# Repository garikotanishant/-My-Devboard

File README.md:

My devboard is a RP2040-based development board designed for prototyping and electronics projects. It features USB-C connectivity, onboard flash memory, a crystal oscillator for precise timing, and multiple GPIO pins for connecting sensors, LEDs, and other components. The board is laid out to support high-speed signals like USB-C while keeping power and ground distribution efficient, making it suitable for a simple microcontroller project! It was very complex for me to build (even with the instructions 😅) but it was a great first project and I learned a lot.

### PCB

### Schematic

##### 3D View

##### PCB parts checkout

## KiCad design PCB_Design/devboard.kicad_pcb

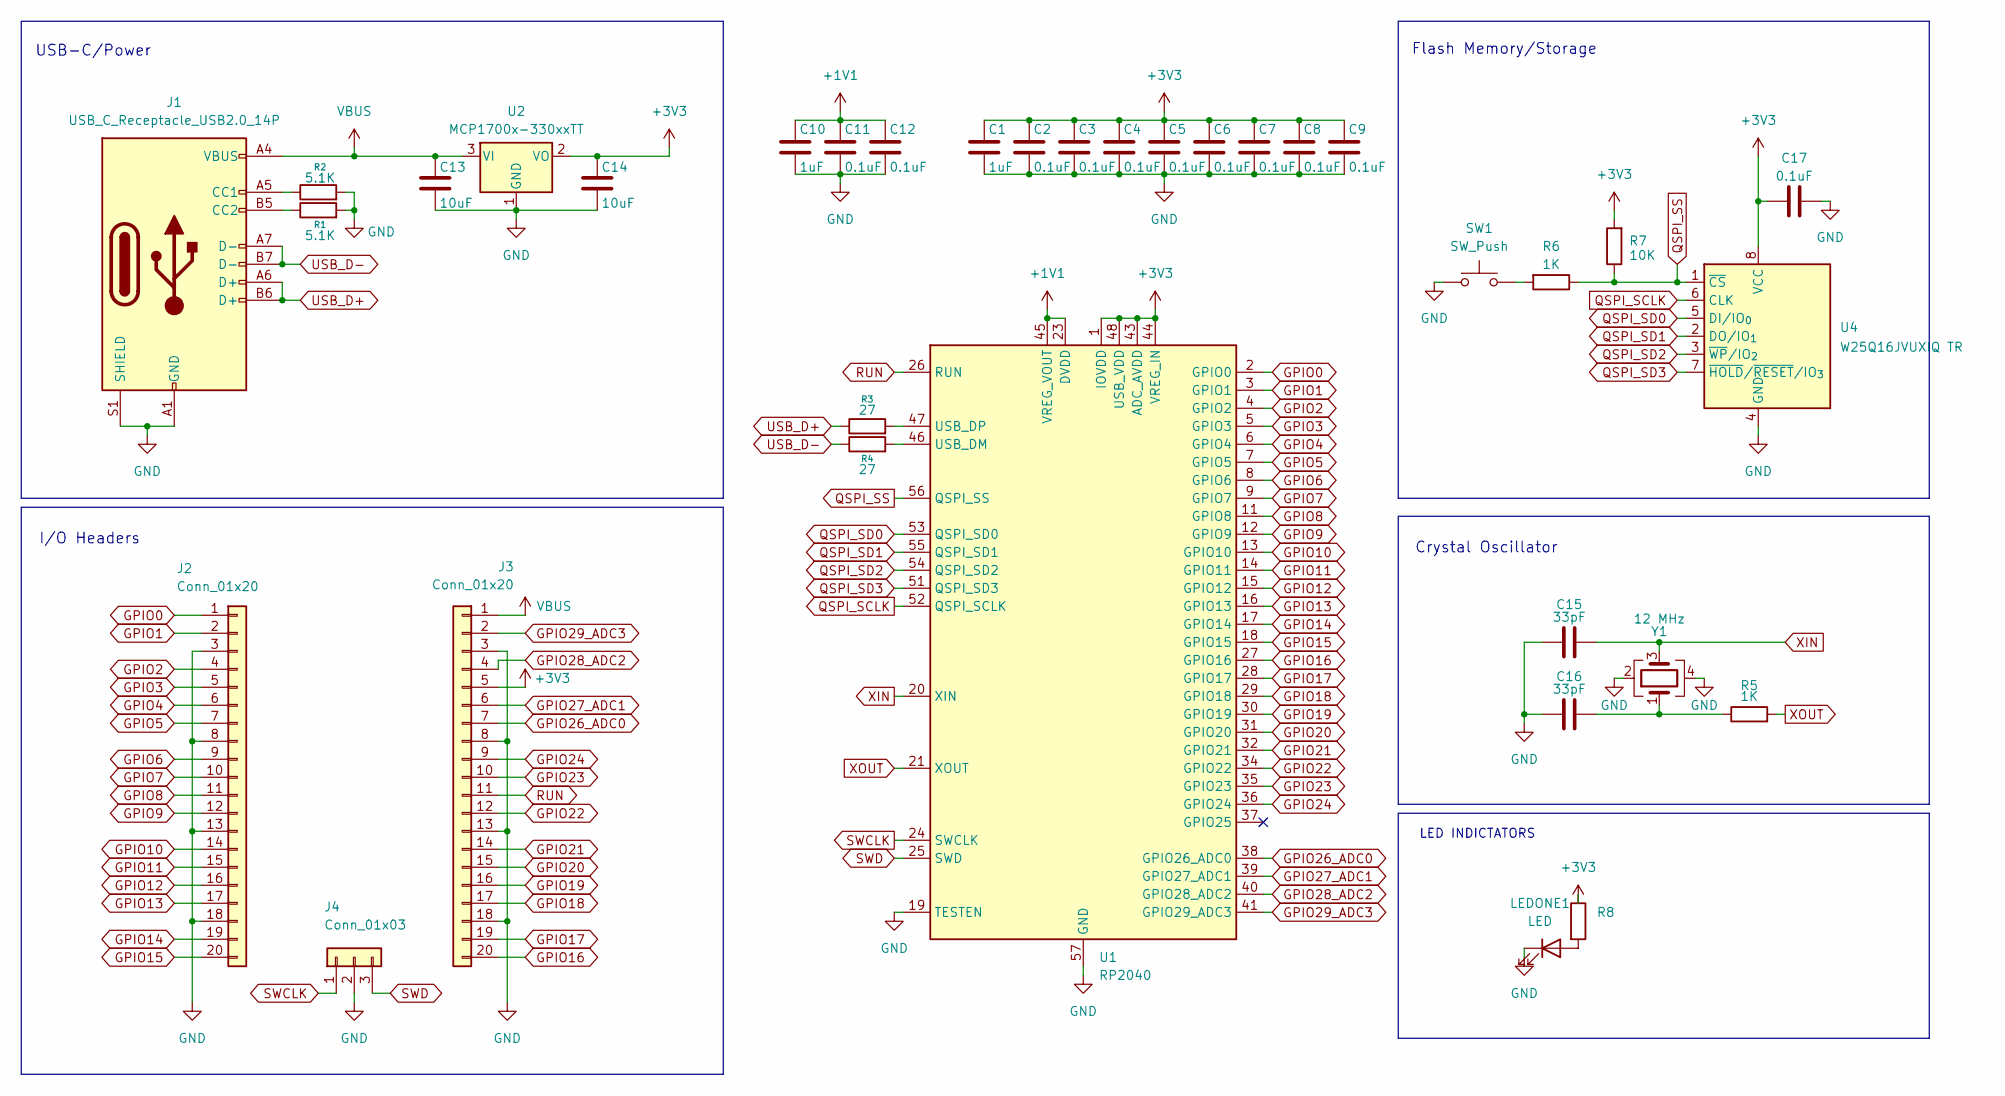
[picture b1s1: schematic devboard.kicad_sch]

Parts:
C1, C10: 1uF; C_0402_1005Metric
C2, C3, C4, C5, C6, C7, C8, C9, C11, C12, C17: 0.1uF; C_0402_1005Metric
C13, C14: 10uF; C_0603_1608Metric
C15, C16: 33pF; C_0402_1005Metric
J1: USB_C_Receptacle_USB2.0_14P; USB_C_Receptacle_HRO_TYPE-C-31-M-12
J2, J3: Conn_01x20; PinHeader_1x20_P2.54mm_Vertical
J4: Conn_01x03; PinHeader_1x03_P2.54mm_Vertical
LEDONE1: LED; LED_0603_1608Metric
R1, R2: 5.1K; R_0402_1005Metric
R3, R4: 27; R_0402_1005Metric
R5, R6: 1K; R_0402_1005Metric
R7: 10K; R_0402_1005Metric
R8: R; R_0603_1608Metric
SW1: SW_Push; SW_Push_SPST_NO_Alps_SKRK
U1: RP2040; QFN-56-1EP_7x7mm_P0.4mm_EP3.2x3.2mm
U2: MCP1700x-330xxTT; SOT-23
U4: W25Q16JVUXIQ TR; Winbond_USON-8-1EP_3x2mm_P0.5mm_EP0.2x1.6mm
Y1: 12 MHz; Crystal_SMD_3225-4Pin_3.2x2.5mm

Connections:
+1V1: C10.1, C11.1, C12.1, U1.23 (DVDD), U1.45 (VREG_VOUT), U1.50 (DVDD)
GND: C1.2, C2.2, C3.2, C4.2, C5.2, C6.2, C7.2, C8.2, C9.2, C10.2, C11.2, C12.2, C13.2, C14.2, C15.1, C16.1, C17.2, J1.A1 (GND), J1.A12 (GND), J1.B1 (GND), J1.B12 (GND), J1.S1 (SHIELD), J2.3, J2.8, J2.13, J2.18, J3.3, J3.8, J3.13, J3.18, J4.2, LEDONE1.1 (K), R1.2, R2.2, SW1.1, U1.19 (TESTEN), U1.57 (GND), U2.1 (GND), U4.4 (GND), Y1.2, Y1.4; also elsewhere on the board
GPIO1: J2.2, U1.3 (GPIO1)
GPIO2: J2.4, U1.4 (GPIO2)
GPIO3: J2.5, U1.5 (GPIO3)
GPIO4: J2.6, U1.6 (GPIO4)
GPIO5: J2.7, U1.7 (GPIO5)
GPIO6: J2.9, U1.8 (GPIO6)
GPIO7: J2.10, U1.9 (GPIO7)
GPIO8: J2.11, U1.11 (GPIO8)
GPIO9: J2.12, U1.12 (GPIO9)
GPIO10: J2.14, U1.13 (GPIO10)
GPIO11: J2.15, U1.14 (GPIO11)
GPIO12: J2.16, U1.15 (GPIO12)
GPIO13: J2.17, U1.16 (GPIO13)
GPIO14: J2.19, U1.17 (GPIO14)
GPIO15: J2.20, U1.18 (GPIO15)
GPIO16: J3.20, U1.27 (GPIO16)
GPIO17: J3.19, U1.28 (GPIO17)
GPIO18: J3.17, U1.29 (GPIO18)
GPIO19: J3.16, U1.30 (GPIO19)
GPIO20: J3.15, U1.31 (GPIO20)
GPIO21: J3.14, U1.32 (GPIO21)
GPIO22: J3.12, U1.34 (GPIO22)
GPIO23: J3.10, U1.35 (GPIO23)
GPIO24: J3.9, U1.36 (GPIO24)
GPIO26_ADC0: J3.7, U1.38 (GPIO26_ADC0)
GPIO27_ADC1: J3.6, U1.39 (GPIO27_ADC1)
GPIO28_ADC2: J3.4, U1.40 (GPIO28_ADC2)
GPIO29_ADC3: J3.2, U1.41 (GPIO29_ADC3)
unnamed: C16.2, R5.1, Y1.1
unnamed: J1.A5 (CC1), R2.1
unnamed: J1.B5 (CC2), R1.1
unnamed: LEDONE1.2 (A), R8.2
unnamed 34: R6.2, SW1.2; also elsewhere on the board
unnamed: R4.2, U1.46 (USB_DM)
unnamed: R3.2, U1.47 (USB_DP)
QSPI_SCLK: U1.52 (QSPI_SCLK), U4.6 (CLK)
QSPI_SD0: U1.53 (QSPI_SD0), U4.5 (DI/IO_{0})
QSPI_SD1: U1.55 (QSPI_SD1), U4.2 (DO/IO_{1})
QSPI_SD2: U1.54 (QSPI_SD2), U4.3 (~WP/IO_{2})
QSPI_SD3: U1.51 (QSPI_SD3), U4.7 (~HOLD/~RESET/IO_{3})
QSPI_SS: R6.1, R7.1, U1.56 (QSPI_SS), U4.1 (~CS)
RUN: J3.11, U1.26 (RUN)
SWCLK: J4.1, U1.24 (SWCLK)
SWD: J4.3, U1.25 (SWD)
USB_D+: J1.A6 (D+), J1.B6 (D+), R3.1
USB_D-: J1.A7 (D-), J1.B7 (D-), R4.1
VBUS: C13.1, J1.A4 (VBUS), J1.A9 (VBUS), J1.B4 (VBUS), J1.B9 (VBUS), J3.1, U2.3 (VI)
XIN: C15.2, U1.20 (XIN), Y1.3
XOUT: R5.2, U1.21 (XOUT)

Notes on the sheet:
Flash Memory/Storage
I/O Headers
LED INDICTATORS
Crystal Oscillator
USB-C/Power

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
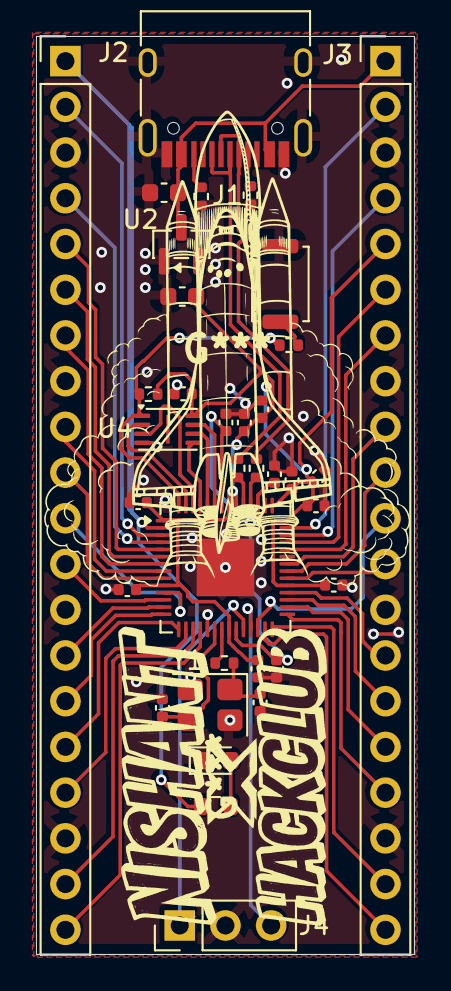
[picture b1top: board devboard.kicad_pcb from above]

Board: 2 copper layers, 21.0 x 51.0 mm, 35 parts (0 on the bottom side), 53 nets.

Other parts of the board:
Boot: SW_Push; SW_Push_SPST_NO_Alps_SKRK

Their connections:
GND: Boot.1; also elsewhere on the board
unnamed 34: Boot.2; also elsewhere on the board

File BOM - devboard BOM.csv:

Id,Designator,Footprint,Quantity,Comment,Supplier and ref
1,"C6,C5,C4,C2,C7,C11,C9,C12,C8,C17,C3",C_0402_1005Metric,11,0.1uF,
2,"C13,C14",C_0603_1608Metric,2,10uF,
16,Y1,Crystal_SMD_3225-4Pin_3.2x2.5mm,1,12 MHz,
4,"C1,C10",C_0402_1005Metric,2,1uF,
5,R7,R_0402_1005Metric,1,10K,
6,"C15,C16",C_0402_1005Metric,2,33pF,
7,"R6,R5",R_0402_1005Metric,2,1K,
8,Boot,SW_Push_SPST_NO_Alps_SKRK,1,SW_Push,
9,J4,PinHeader_1x03_P2.54mm_Vertical,1,J4,
10,"R2,R1",R_0402_1005Metric,2,5.1K,
11,"R3,R4",R_0402_1005Metric,2,27,
12,U1,QFN-56-1EP_7x7mm_P0.4mm_EP3.2x3.2mm,1,RP2040,
13,J1,USB_C_Receptacle_HRO_TYPE-C-31-M-12,1,USB_C_Receptacle_USB2.0_14P,
14,"J3,J2",PinHeader_1x20_P2.54mm_Vertical,2,Conn_01x20,
15,U2,SOT-23,1,MCP1700x-330xxTT,
,U4,Winbond_USON-8-1EP_3x2mm_P0.5mm_EP0.2x1.6mm,1,W25Q16JVUXIQ TR,

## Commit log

2025-12-06 Create pcb
2025-12-08 Create PRODUCTION
2025-12-08 Create GRBR's
